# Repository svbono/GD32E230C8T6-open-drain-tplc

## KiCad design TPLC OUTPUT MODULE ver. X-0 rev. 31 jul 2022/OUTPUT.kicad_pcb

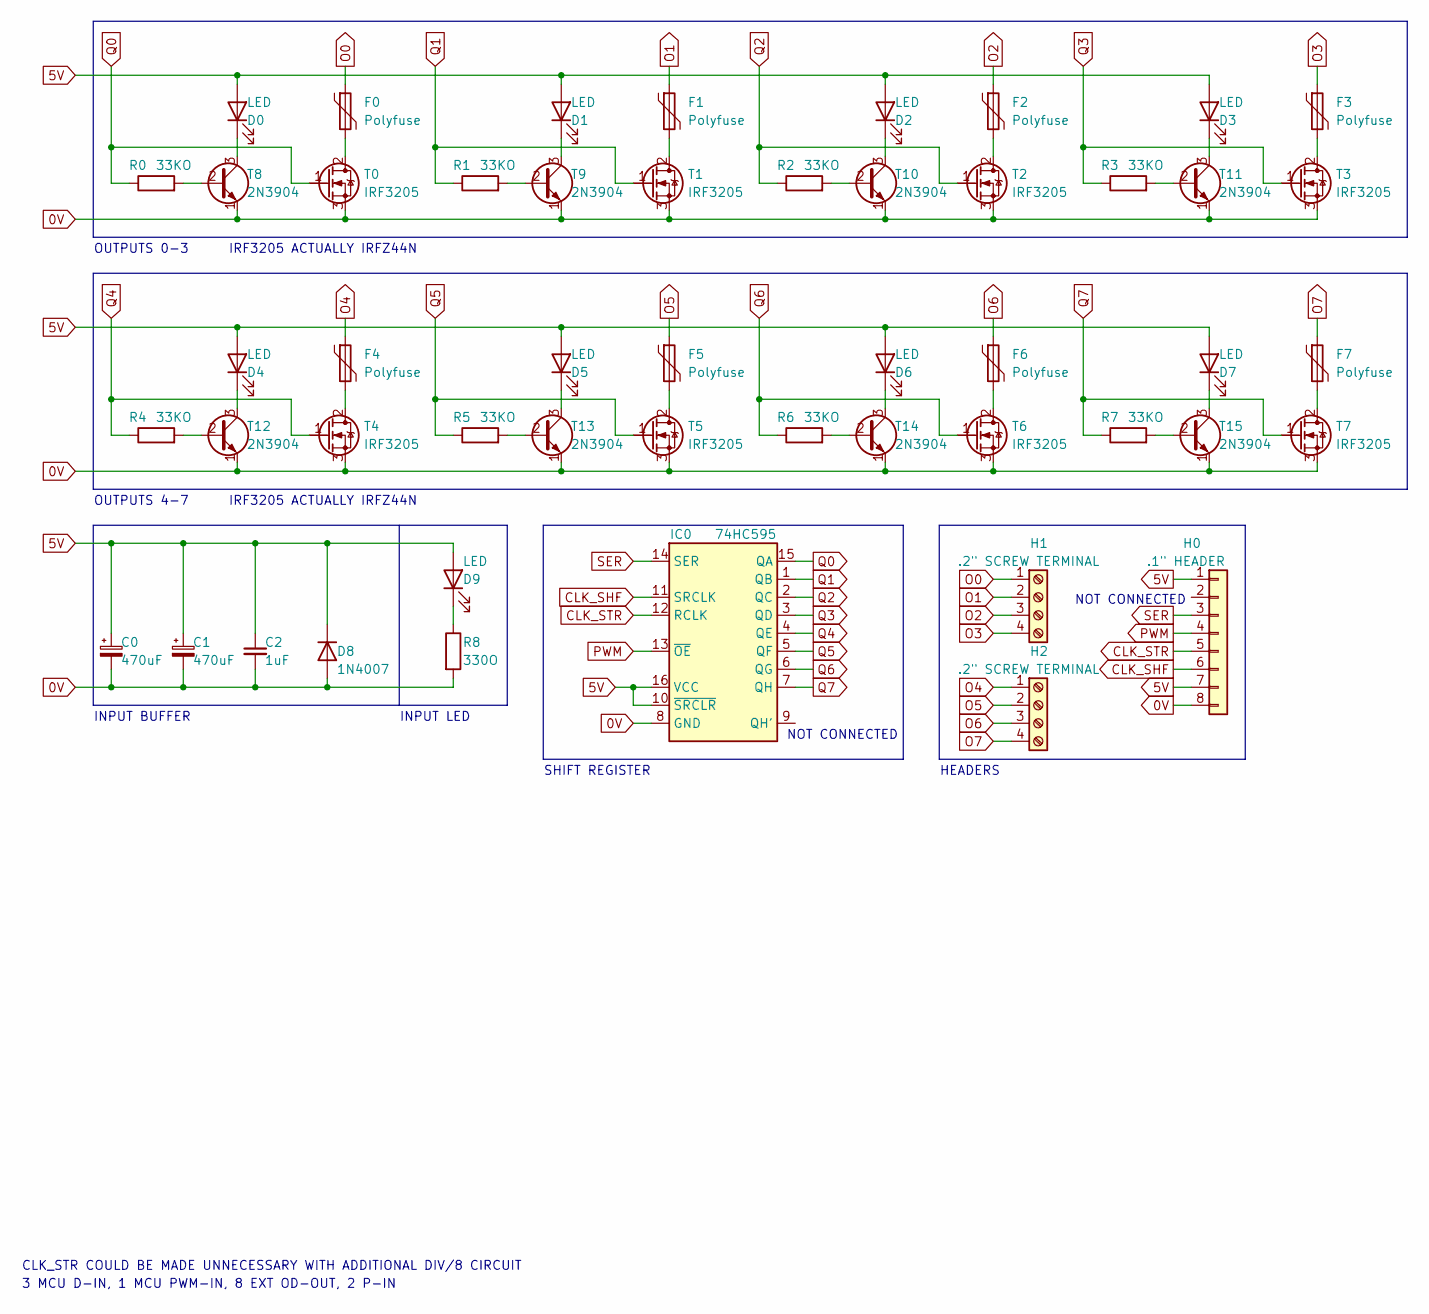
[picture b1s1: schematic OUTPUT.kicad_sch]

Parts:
C0, C1: 470uF; C_Radial_D.4in_P.1in
C2: 1uF; C_L.3in_W.1in_P.2in
D0, D1, D2, D3, D4, D5, D6, D7, D9: LED; LED_L.2in_W.1in_P.1in
D8: 1N4007; D_L.4in_W.1in_P.3in
F0, F1, F2, F3, F4, F5, F6, F7: Polyfuse; F_L1.2in_W.1in_P.4in
H0: .1" HEADER; H_1x8_P.1in
H1, H2: .2" SCREW TERMINAL; H_P.2in_4pin
IC0: 74HC595; DIP-16_W7.62mm_Short
R0, R1, R2, R3, R4, R5, R6, R7: 33KO; R_L.4in_W.1in_P.3in
R8: 330O; R_L.4in_W.1in_P.3in
T0, T1, T2, T3, T4, T5, T6, T7: IRF3205; TO-220-3_Horizontal_TabDown
T8, T9, T10, T11, T12, T13, T14, T15: 2N3904; TO-92L_Inline_Wide

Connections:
0V: C0.2, C1.2, C2.2, D8.2 (A), H0.8, IC0.8 (GND), R8.2, T0.3 (S), T1.3 (S), T2.3 (S), T3.3 (S), T4.3 (S), T5.3 (S), T6.3 (S), T7.3 (S), T8.1 (E), T9.1 (E), T10.1 (E), T11.1 (E), T12.1 (E), T13.1 (E), T14.1 (E), T15.1 (E)
3.3V: C0.1, C1.1, C2.1, D0.2 (A), D1.2 (A), D2.2 (A), D3.2 (A), D4.2 (A), D5.2 (A), D6.2 (A), D7.2 (A), D8.1 (K), D9.2 (A), H0.1, H0.7, IC0.10 (~SRCLR), IC0.16 (VCC)
CLK_SHF: H0.6, IC0.11 (SRCLK)
CLK_STR: H0.5, IC0.12 (RCLK)
unnamed: D0.1 (K), T8.3 (C)
unnamed: D1.1 (K), T9.3 (C)
unnamed: D2.1 (K), T10.3 (C)
unnamed: D3.1 (K), T11.3 (C)
unnamed: D4.1 (K), T12.3 (C)
unnamed: D5.1 (K), T13.3 (C)
unnamed: D6.1 (K), T14.3 (C)
unnamed: D7.1 (K), T15.3 (C)
unnamed: D9.1 (K), R8.1
unnamed: F0.2, T0.2 (D)
unnamed: F1.2, T1.2 (D)
unnamed: F2.2, T2.2 (D)
unnamed: F3.2, T3.2 (D)
unnamed: F4.2, T4.2 (D)
unnamed: F5.2, T5.2 (D)
unnamed: F6.2, T6.2 (D)
unnamed: F7.2, T7.2 (D)
unnamed: R0.2, T8.2 (B)
unnamed: R1.2, T9.2 (B)
unnamed: R2.2, T10.2 (B)
unnamed: R3.2, T11.2 (B)
unnamed: R4.2, T12.2 (B)
unnamed: R5.2, T13.2 (B)
unnamed: R6.2, T14.2 (B)
unnamed: R7.2, T15.2 (B)
O0: F0.1, H1.1
O1: F1.1, H1.2
O2: F2.1, H1.3
O3: F3.1, H1.4
O4: F4.1, H2.1
O5: F5.1, H2.2
O6: F6.1, H2.3
O7: F7.1, H2.4
PWM: H0.4, IC0.13 (~OE)
Q0: IC0.15 (QA), R0.1, T0.1 (G)
Q1: IC0.1 (QB), R1.1, T1.1 (G)
Q2: IC0.2 (QC), R2.1, T2.1 (G)
Q3: IC0.3 (QD), R3.1, T3.1 (G)
Q4: IC0.4 (QE), R4.1, T4.1 (G)
Q5: IC0.5 (QF), R5.1, T5.1 (G)
Q6: IC0.6 (QG), R6.1, T6.1 (G)
Q7: IC0.7 (QH), R7.1, T7.1 (G)
SER: H0.3, IC0.14 (SER)

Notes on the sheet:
IRF3205 ACTUALLY IRFZ44N
NOT CONNECTED
INPUT BUFFER
SHIFT REGISTER
INPUT LED
OUTPUTS 0-3
CLK_STR COULD BE MADE UNNECESSARY WITH ADDITIONAL DIV/8 CIRCUIT
HEADERS
OUTPUTS 4-7
3 MCU D-IN, 1 MCU PWM-IN, 8 EXT OD-OUT, 2 P-IN

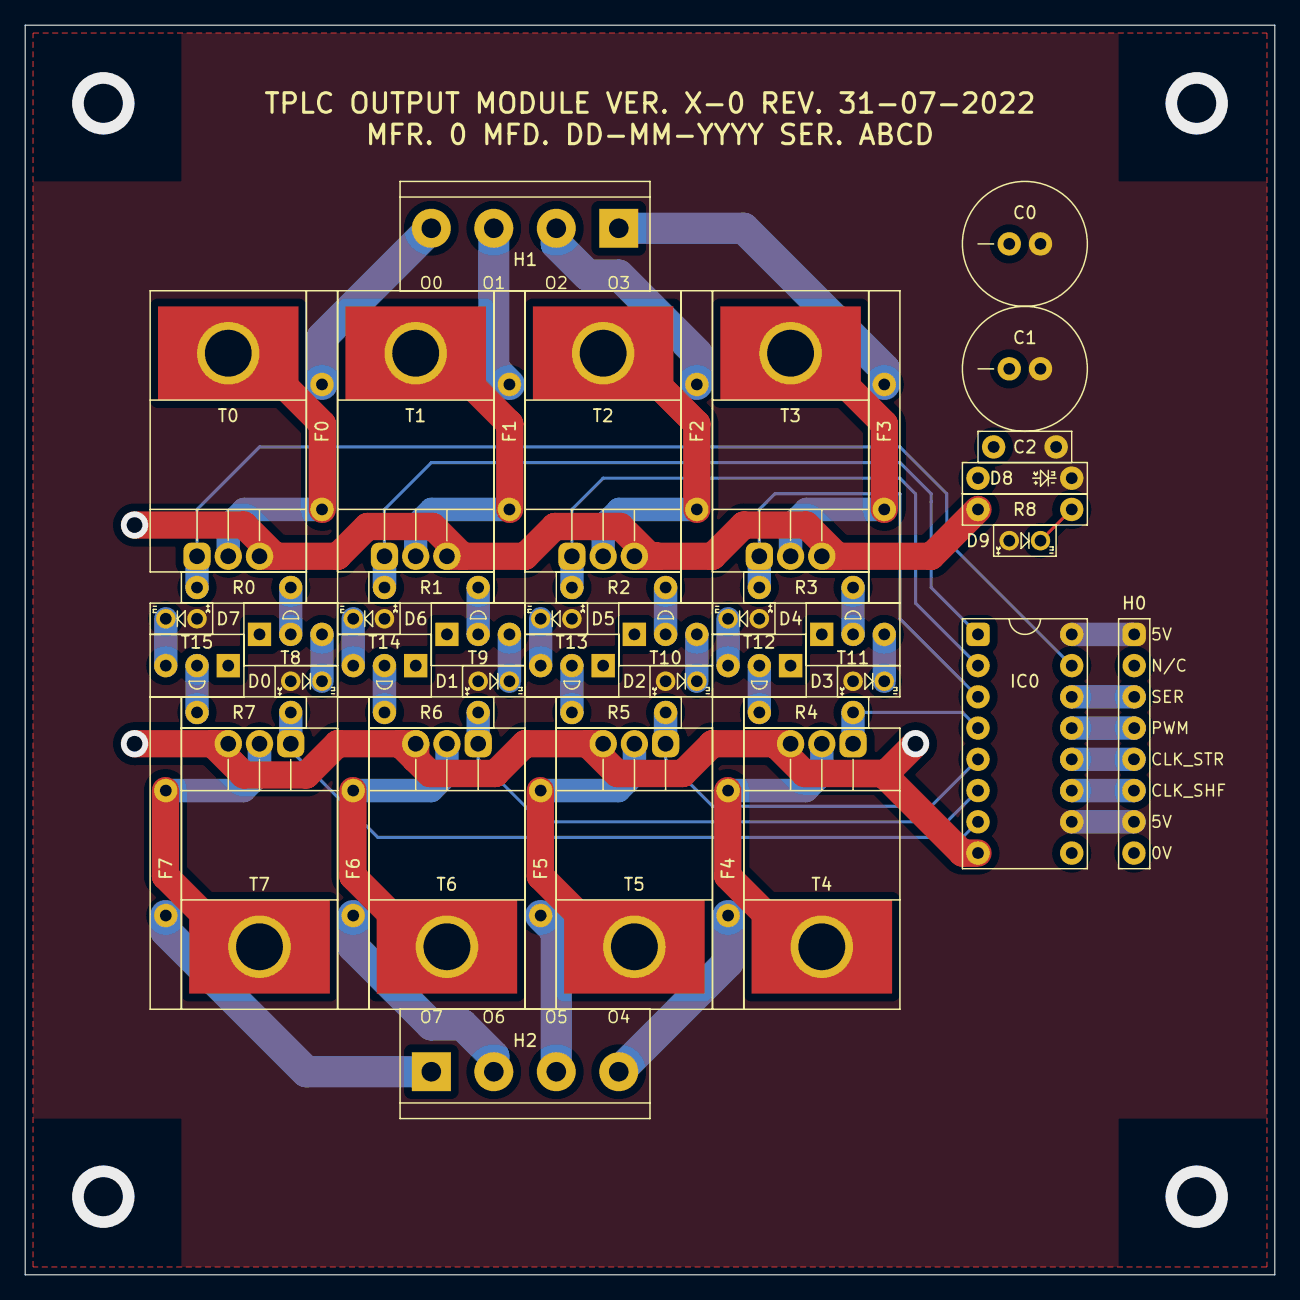
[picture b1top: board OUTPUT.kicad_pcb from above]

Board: 2 copper layers, 101.6 x 101.6 mm, 50 parts (0 on the bottom side), 47 nets.

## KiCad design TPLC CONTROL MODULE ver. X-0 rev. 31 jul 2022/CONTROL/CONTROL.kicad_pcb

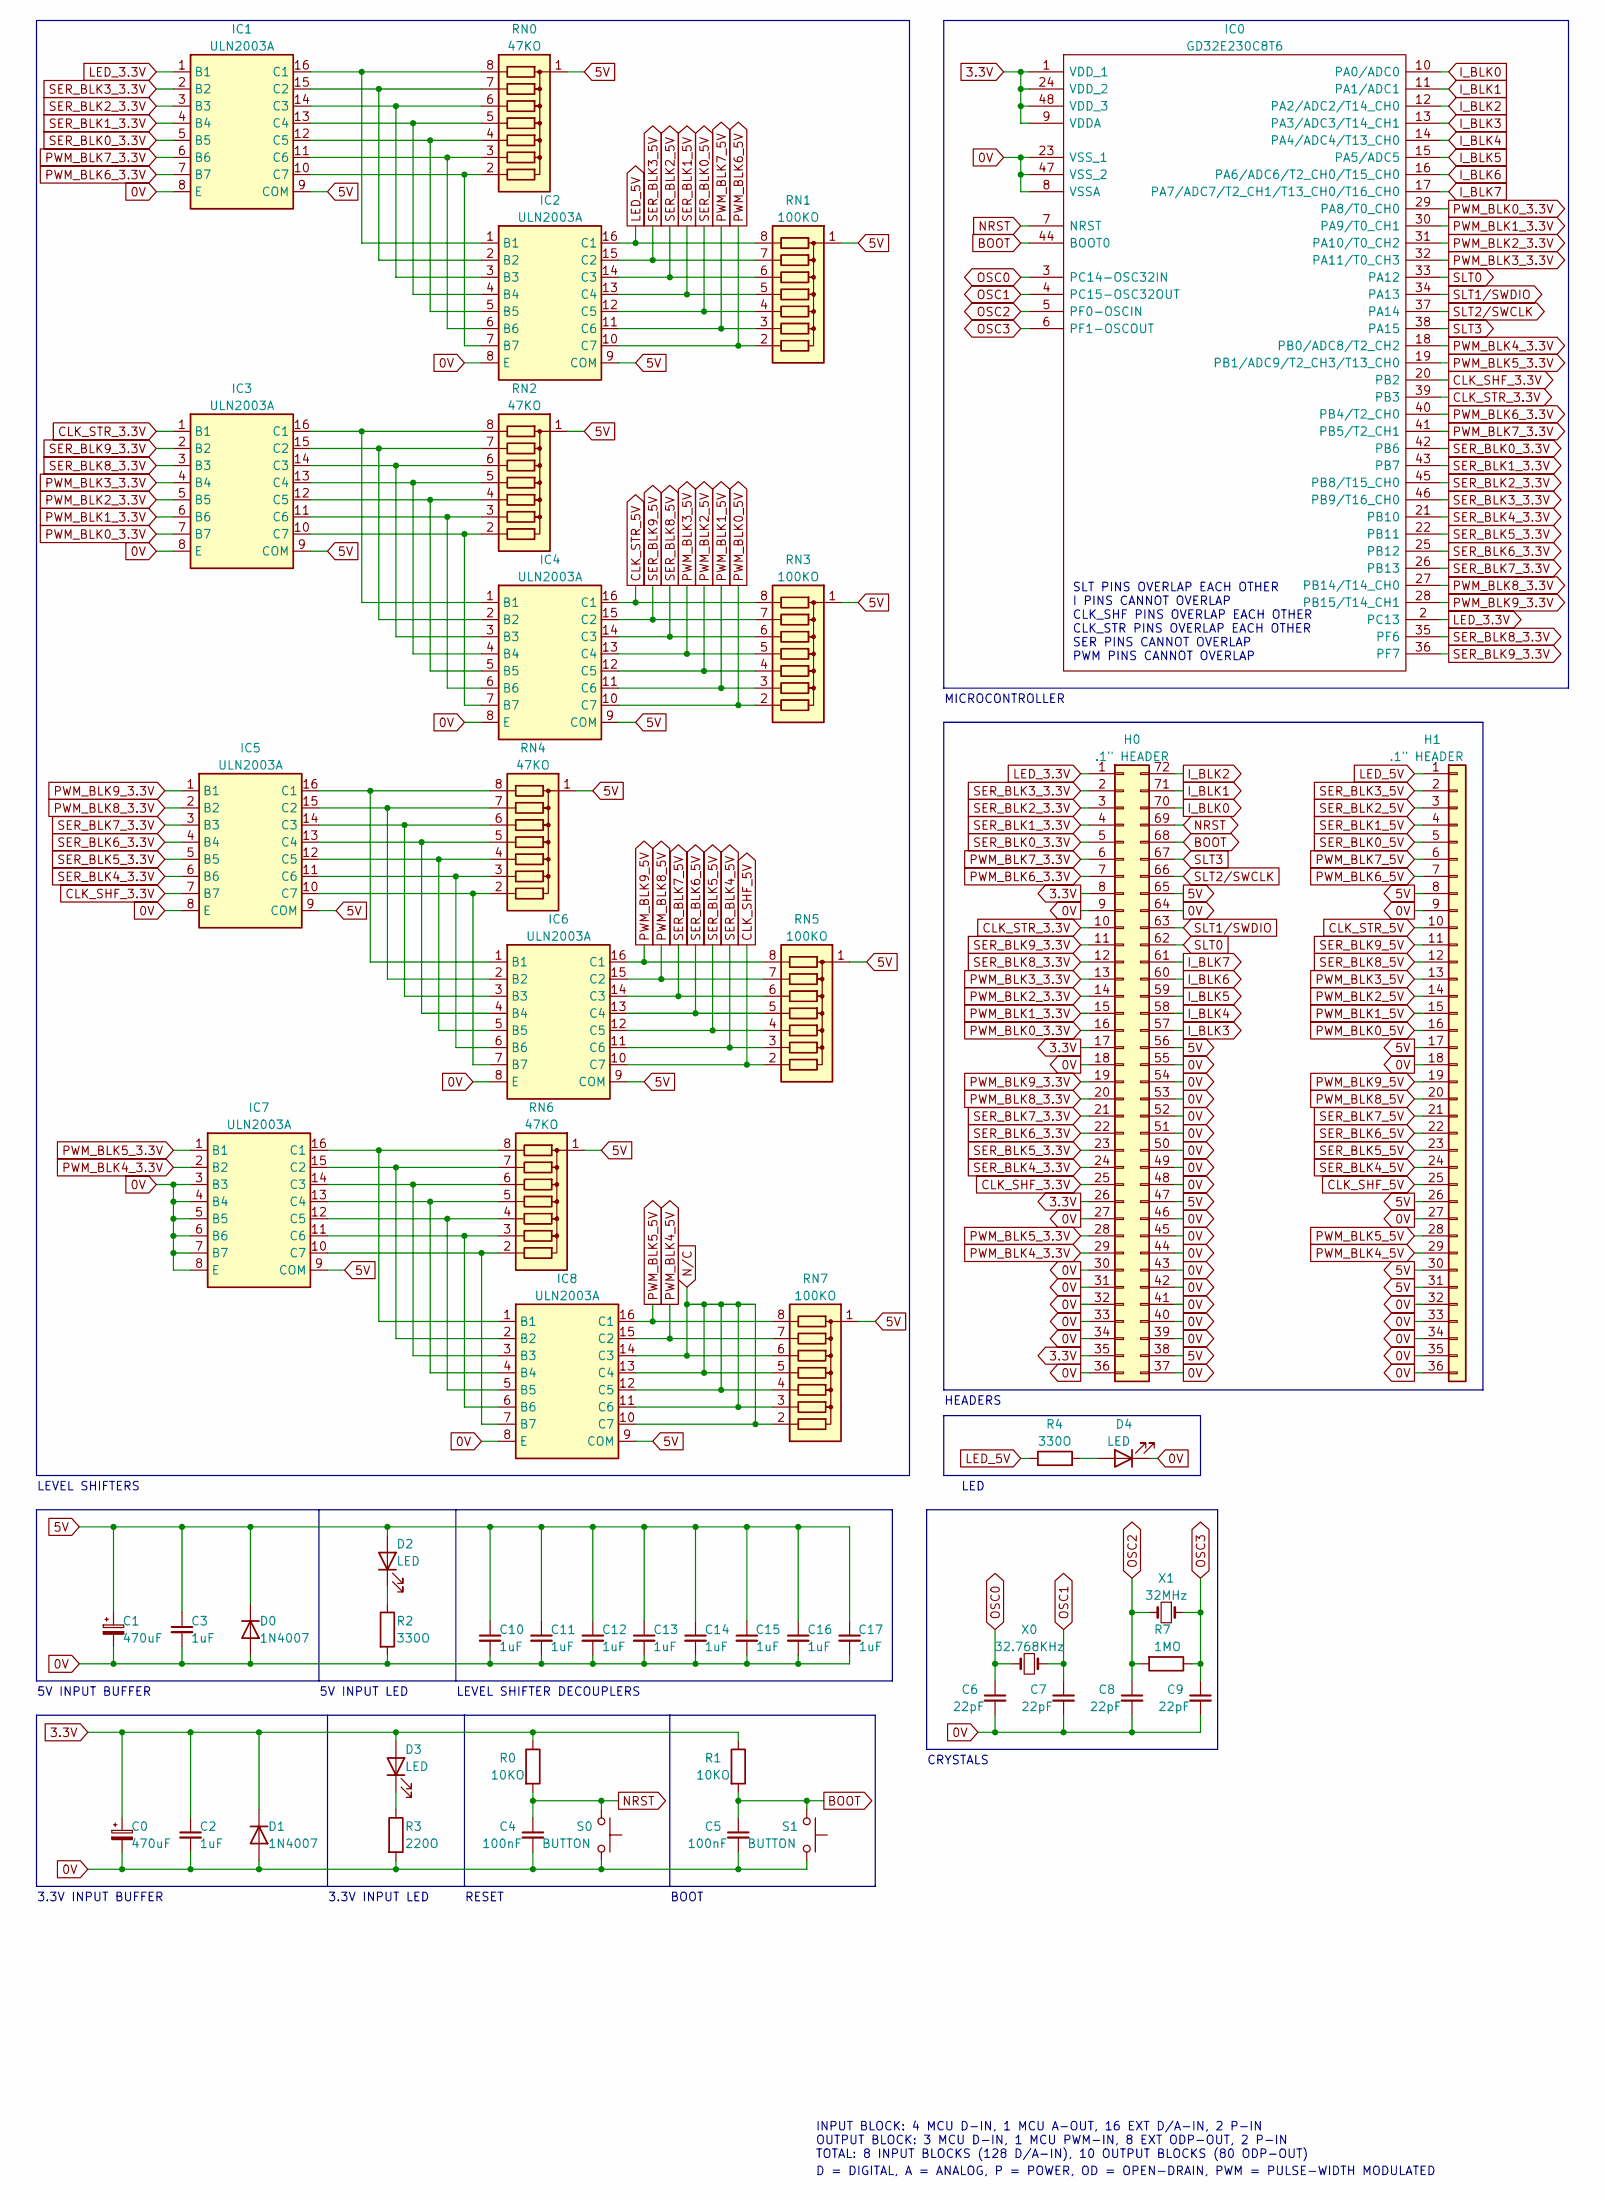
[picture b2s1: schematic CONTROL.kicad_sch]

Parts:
C0, C1: 470uF; C_Radial_D.4in_P.1in
C2, C3, C10, C11, C12, C13, C14, C15, C16, C17: 1uF; C_L.3in_W.1in_P.2in
C4, C5: 100nF; C_L.3in_W.1in_P.2in
C6, C7, C8, C9: 22pF; C_L.3in_W.1in_P.2in
D0, D1: 1N4007; D_L.4in_W.1in_P.3in
D2, D3, D4: LED; LED_L.2in_W.1in_P.1in
H0: .1" HEADER; H_2x36_P.1in
H1: .1" HEADER; H_1x36_P.1in
IC0: GD32E230C8T6; QFN-48-1EP_7x7mm_P0.5mm_EP5.15x5.15mm; Manufacturer_Part_Number GD32E230C8T6; Mouser Part Number N/A
IC1, IC2, IC3, IC4, IC5, IC6, IC7, IC8: ULN2003A; DIP-16_W7.62mm_Short
R0, R1: 10KO; R_L.4in_W.1in_P.3in
R2, R4: 330O; R_L.4in_W.1in_P.3in
R3: 220O; R_L.4in_W.1in_P.3in
R7: 1MO; R_L.4in_W.1in_P.3in
RN0, RN2, RN4, RN6: 47KO; R_SIP8
RN1, RN3, RN5, RN7: 100KO; R_SIP8
S0, S1: BUTTON; J_L.4in_W.1in_P.3in
X0: 32.768KHz; X_L.5in_W.2in_P.2in
X1: 32MHz; X_L.5in_W.2in_P.2in

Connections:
0V: C0.2, C1.2, C2.2, C3.2, C4.2, C5.2, C6.2, C7.2, C8.2, C9.2, C10.2, C11.2, C12.2, C13.2, C14.2, C15.2, C16.2, C17.2, D0.2 (A), D1.2 (A), D4.1 (K), H0.9, H0.18, H0.27, H0.30, H0.31, H0.32, H0.33, H0.34, H0.36, H0.37, H0.39, H0.40, H0.41, H0.42, H0.43, H0.44, H0.45, H0.46, H0.48, H0.49, H0.50, H0.51, H0.52, H0.53, H0.54, H0.55, H0.64, H1.9, H1.18, H1.27, H1.32, H1.33, H1.34, H1.35, H1.36, IC0.8 (VSSA), IC0.23 (VSS_1), IC0.47 (VSS_2), IC1.8 (E), IC2.8 (E), IC3.8 (E), IC4.8 (E), IC5.8 (E), IC6.8 (E), IC7.3 (B3), IC7.4 (B4), IC7.5 (B5), IC7.6 (B6), IC7.7 (B7), IC7.8 (E), IC8.8 (E), R2.2, R3.2, S0.2, S1.2
3.3V: C0.1, C2.1, D1.1 (K), D3.2 (A), H0.8, H0.17, H0.26, H0.35, IC0.1 (VDD_1), IC0.9 (VDDA), IC0.24 (VDD_2), IC0.48 (VDD_3), R0.1, R1.1
5V: C1.1, C3.1, C10.1, C11.1, C12.1, C13.1, C14.1, C15.1, C16.1, C17.1, D0.1 (K), D2.2 (A), H0.38, H0.47, H0.56, H0.65, H1.8, H1.17, H1.26, H1.30, H1.31, IC1.9 (COM), IC2.9 (COM), IC3.9 (COM), IC4.9 (COM), IC5.9 (COM), IC6.9 (COM), IC7.9 (COM), IC8.9 (COM), RN0.1 (common), RN1.1 (common), RN2.1 (common), RN3.1 (common), RN4.1 (common), RN5.1 (common), RN6.1 (common), RN7.1 (common)
BOOT: C5.1, H0.68, IC0.44 (BOOT0), R1.2, S1.1
CLK_SHF_3.3V: H0.25, IC0.20 (PB2), IC5.7 (B7)
CLK_SHF_5V: H1.25, IC6.10 (C7), RN5.2 (R7)
CLK_STR_3.3V: H0.10, IC0.39 (PB3), IC3.1 (B1)
CLK_STR_5V: H1.10, IC4.16 (C1), RN3.8 (R1)
I_BLK0: H0.70, IC0.10 (PA0/ADC0)
I_BLK1: H0.71, IC0.11 (PA1/ADC1)
I_BLK2: H0.72, IC0.12 (PA2/ADC2/T14_CH0)
I_BLK3: H0.57, IC0.13 (PA3/ADC3/T14_CH1)
I_BLK4: H0.58, IC0.14 (PA4/ADC4/T13_CH0)
I_BLK5: H0.59, IC0.15 (PA5/ADC5)
I_BLK6: H0.60, IC0.16 (PA6/ADC6/T2_CH0/T15_CH0)
I_BLK7: H0.61, IC0.17 (PA7/ADC7/T2_CH1/T13_CH0/T16_CH0)
LED_3.3V: H0.1, IC0.2 (PC13), IC1.1 (B1)
LED_5V: H1.1, IC2.16 (C1), R4.1, RN1.8 (R1)
NRST: C4.1, H0.69, IC0.7 (NRST), R0.2, S0.1
unnamed: D2.1 (K), R2.1
unnamed: D3.1 (K), R3.1
unnamed: D4.2 (A), R4.2
unnamed: IC1.10 (C7), IC2.7 (B7), RN0.2 (R7)
unnamed: IC1.11 (C6), IC2.6 (B6), RN0.3 (R6)
unnamed: IC1.12 (C5), IC2.5 (B5), RN0.4 (R5)
unnamed: IC1.13 (C4), IC2.4 (B4), RN0.5 (R4)
unnamed: IC1.14 (C3), IC2.3 (B3), RN0.6 (R3)
unnamed: IC1.15 (C2), IC2.2 (B2), RN0.7 (R2)
unnamed: IC1.16 (C1), IC2.1 (B1), RN0.8 (R1)
unnamed: IC3.10 (C7), IC4.7 (B7), RN2.2 (R7)
unnamed: IC3.11 (C6), IC4.6 (B6), RN2.3 (R6)
unnamed: IC3.12 (C5), IC4.5 (B5), RN2.4 (R5)
unnamed: IC3.13 (C4), IC4.4 (B4), RN2.5 (R4)
unnamed: IC3.14 (C3), IC4.3 (B3), RN2.6 (R3)
unnamed: IC3.15 (C2), IC4.2 (B2), RN2.7 (R2)
unnamed: IC3.16 (C1), IC4.1 (B1), RN2.8 (R1)
unnamed: IC5.10 (C7), IC6.7 (B7), RN4.2 (R7)
unnamed: IC5.11 (C6), IC6.6 (B6), RN4.3 (R6)
unnamed: IC5.12 (C5), IC6.5 (B5), RN4.4 (R5)
unnamed: IC5.13 (C4), IC6.4 (B4), RN4.5 (R4)
unnamed: IC5.14 (C3), IC6.3 (B3), RN4.6 (R3)
unnamed: IC5.15 (C2), IC6.2 (B2), RN4.7 (R2)
unnamed: IC5.16 (C1), IC6.1 (B1), RN4.8 (R1)
unnamed: IC7.10 (C7), IC8.7 (B7), RN6.2 (R7)
unnamed: IC7.11 (C6), IC8.6 (B6), RN6.3 (R6)
unnamed: IC7.12 (C5), IC8.5 (B5), RN6.4 (R5)
unnamed: IC7.13 (C4), IC8.4 (B4), RN6.5 (R4)
unnamed: IC7.14 (C3), IC8.3 (B3), RN6.6 (R3)
unnamed: IC7.15 (C2), IC8.2 (B2), RN6.7 (R2)
unnamed: IC7.16 (C1), IC8.1 (B1), RN6.8 (R1)
N/C: IC8.10 (C7), IC8.11 (C6), IC8.12 (C5), IC8.13 (C4), IC8.14 (C3), RN7.2 (R7), RN7.3 (R6), RN7.4 (R5), RN7.5 (R4), RN7.6 (R3)
OSC0: C6.1, IC0.3 (PC14-OSC32IN), X0.2
OSC1: C7.1, IC0.4 (PC15-OSC32OUT), X0.1
OSC2: C8.1, IC0.5 (PF0-OSCIN), R7.2, X1.2
OSC3: C9.1, IC0.6 (PF1-OSCOUT), R7.1, X1.1
PWM_BLK0_3.3V: H0.16, IC0.29 (PA8/T0_CH0), IC3.7 (B7)
PWM_BLK0_5V: H1.16, IC4.10 (C7), RN3.2 (R7)
PWM_BLK1_3.3V: H0.15, IC0.30 (PA9/T0_CH1), IC3.6 (B6)
PWM_BLK1_5V: H1.15, IC4.11 (C6), RN3.3 (R6)
PWM_BLK2_3.3V: H0.14, IC0.31 (PA10/T0_CH2), IC3.5 (B5)
PWM_BLK2_5V: H1.14, IC4.12 (C5), RN3.4 (R5)
PWM_BLK3_3.3V: H0.13, IC0.32 (PA11/T0_CH3), IC3.4 (B4)
PWM_BLK3_5V: H1.13, IC4.13 (C4), RN3.5 (R4)
PWM_BLK4_3.3V: H0.29, IC0.18 (PB0/ADC8/T2_CH2), IC7.2 (B2)
PWM_BLK4_5V: H1.29, IC8.15 (C2), RN7.7 (R2)
PWM_BLK5_3.3V: H0.28, IC0.19 (PB1/ADC9/T2_CH3/T13_CH0), IC7.1 (B1)
PWM_BLK5_5V: H1.28, IC8.16 (C1), RN7.8 (R1)
PWM_BLK6_3.3V: H0.7, IC0.40 (PB4/T2_CH0), IC1.7 (B7)
PWM_BLK6_5V: H1.7, IC2.10 (C7), RN1.2 (R7)
PWM_BLK7_3.3V: H0.6, IC0.41 (PB5/T2_CH1), IC1.6 (B6)
PWM_BLK7_5V: H1.6, IC2.11 (C6), RN1.3 (R6)
PWM_BLK8_3.3V: H0.20, IC0.27 (PB14/T14_CH0), IC5.2 (B2)
PWM_BLK8_5V: H1.20, IC6.15 (C2), RN5.7 (R2)
PWM_BLK9_3.3V: H0.19, IC0.28 (PB15/T14_CH1), IC5.1 (B1)
PWM_BLK9_5V: H1.19, IC6.16 (C1), RN5.8 (R1)
SER_BLK0_3.3V: H0.5, IC0.42 (PB6), IC1.5 (B5)
SER_BLK0_5V: H1.5, IC2.12 (C5), RN1.4 (R5)
SER_BLK1_3.3V: H0.4, IC0.43 (PB7), IC1.4 (B4)
SER_BLK1_5V: H1.4, IC2.13 (C4), RN1.5 (R4)
SER_BLK2_3.3V: H0.3, IC0.45 (PB8/T15_CH0), IC1.3 (B3)
SER_BLK2_5V: H1.3, IC2.14 (C3), RN1.6 (R3)
SER_BLK3_3.3V: H0.2, IC0.46 (PB9/T16_CH0), IC1.2 (B2)
SER_BLK3_5V: H1.2, IC2.15 (C2), RN1.7 (R2)
SER_BLK4_3.3V: H0.24, IC0.21 (PB10), IC5.6 (B6)
SER_BLK4_5V: H1.24, IC6.11 (C6), RN5.3 (R6)
SER_BLK5_3.3V: H0.23, IC0.22 (PB11), IC5.5 (B5)
SER_BLK5_5V: H1.23, IC6.12 (C5), RN5.4 (R5)
SER_BLK6_3.3V: H0.22, IC0.25 (PB12), IC5.4 (B4)
SER_BLK6_5V: H1.22, IC6.13 (C4), RN5.5 (R4)
SER_BLK7_3.3V: H0.21, IC0.26 (PB13), IC5.3 (B3)
SER_BLK7_5V: H1.21, IC6.14 (C3), RN5.6 (R3)
SER_BLK8_3.3V: H0.12, IC0.35 (PF6), IC3.3 (B3)
SER_BLK8_5V: H1.12, IC4.14 (C3), RN3.6 (R3)
SER_BLK9_3.3V: H0.11, IC0.36 (PF7), IC3.2 (B2)
SER_BLK9_5V: H1.11, IC4.15 (C2), RN3.7 (R2)
SLT0: H0.62, IC0.33 (PA12)
SLT1/SWDIO: H0.63, IC0.34 (PA13)
SLT2/SWCLK: H0.66, IC0.37 (PA14)
SLT3: H0.67, IC0.38 (PA15)

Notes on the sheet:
MICROCONTROLLER
LEVEL SHIFTER DECOUPLERS
SLT PINS OVERLAP EACH OTHER I PINS CANNOT OVERLAP CLK_SHF PINS OVERLAP EACH OTHER CLK_STR PINS OVERLAP EACH OTHER SER PINS CANNOT OVERLAP PWM PINS CANNOT OVERLAP
LEVEL SHIFTERS
D = DIGITAL, A = ANALOG, P = POWER, OD = OPEN-DRAIN, PWM = PULSE-WIDTH MODULATED
RESET
3.3V INPUT LED
INPUT BLOCK: 4 MCU D-IN, 1 MCU A-OUT, 16 EXT D/A-IN, 2 P-IN OUTPUT BLOCK: 3 MCU D-IN, 1 MCU PWM-IN, 8 EXT ODP-OUT, 2 P-IN TOTAL: 8 INPUT BLOCKS (128 D/A-IN), 10 OUTPUT BLOCKS (80 ODP-OUT)
5V INPUT LED
LED
5V INPUT BUFFER
CRYSTALS
BOOT
HEADERS
3.3V INPUT BUFFER

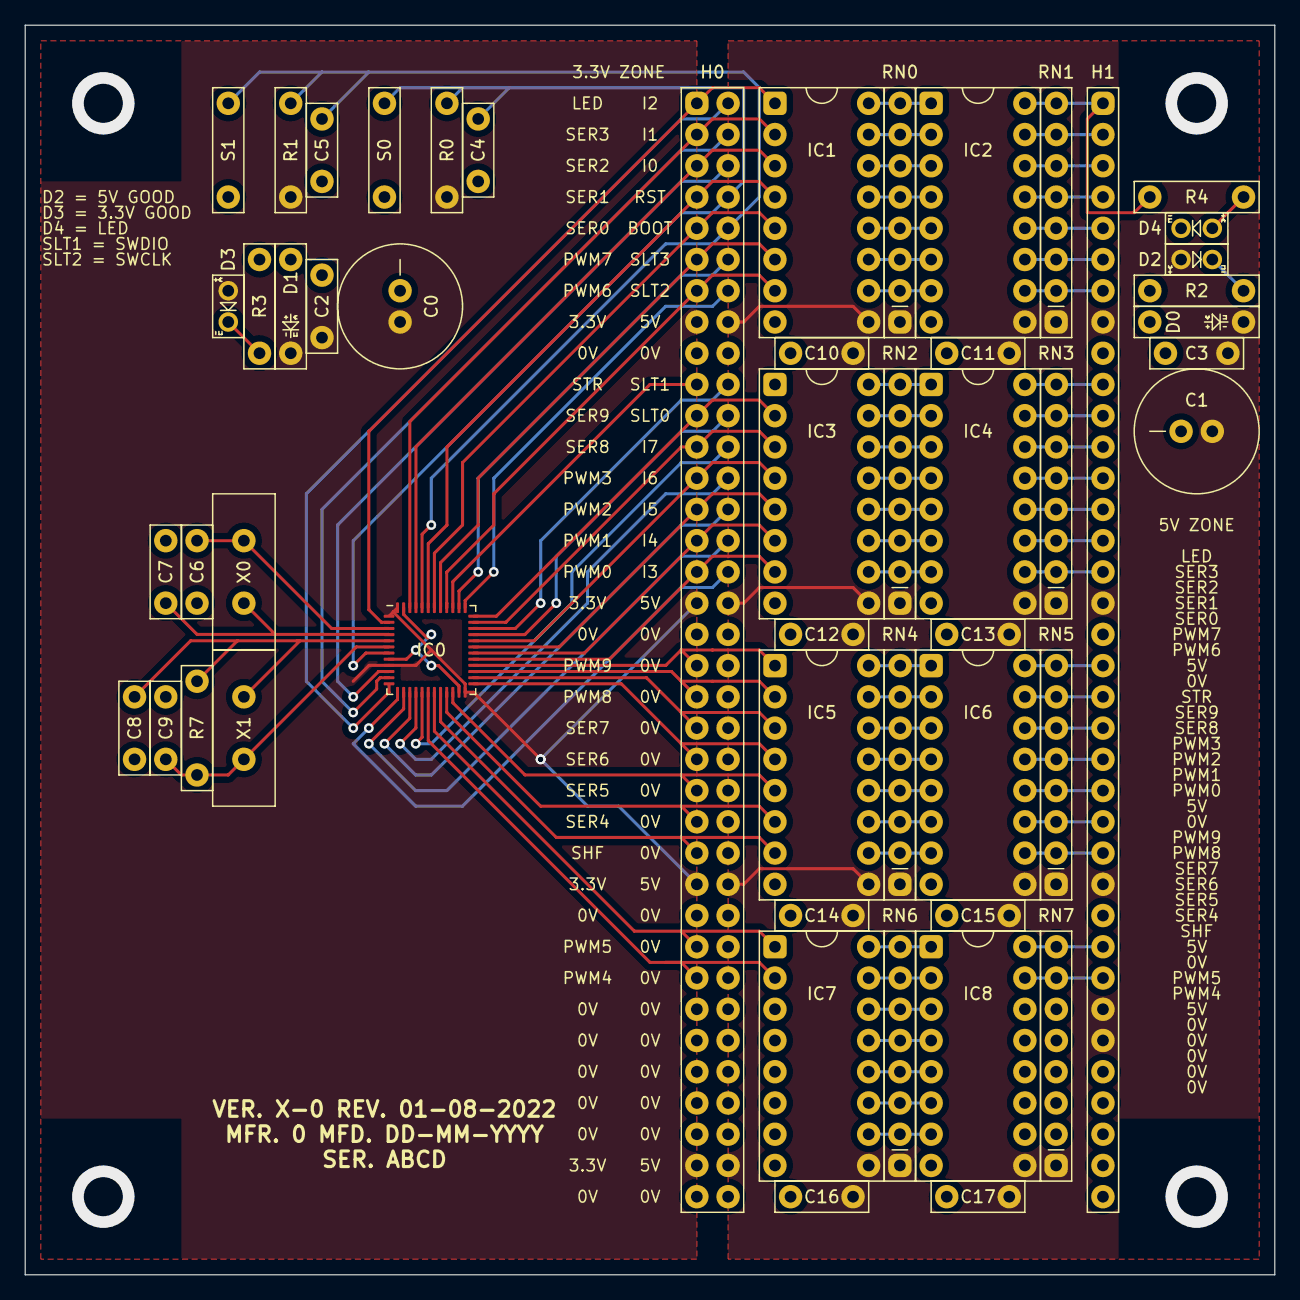
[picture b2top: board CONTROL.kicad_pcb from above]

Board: 2 copper layers, 101.6 x 101.6 mm, 52 parts (0 on the bottom side), 99 nets.

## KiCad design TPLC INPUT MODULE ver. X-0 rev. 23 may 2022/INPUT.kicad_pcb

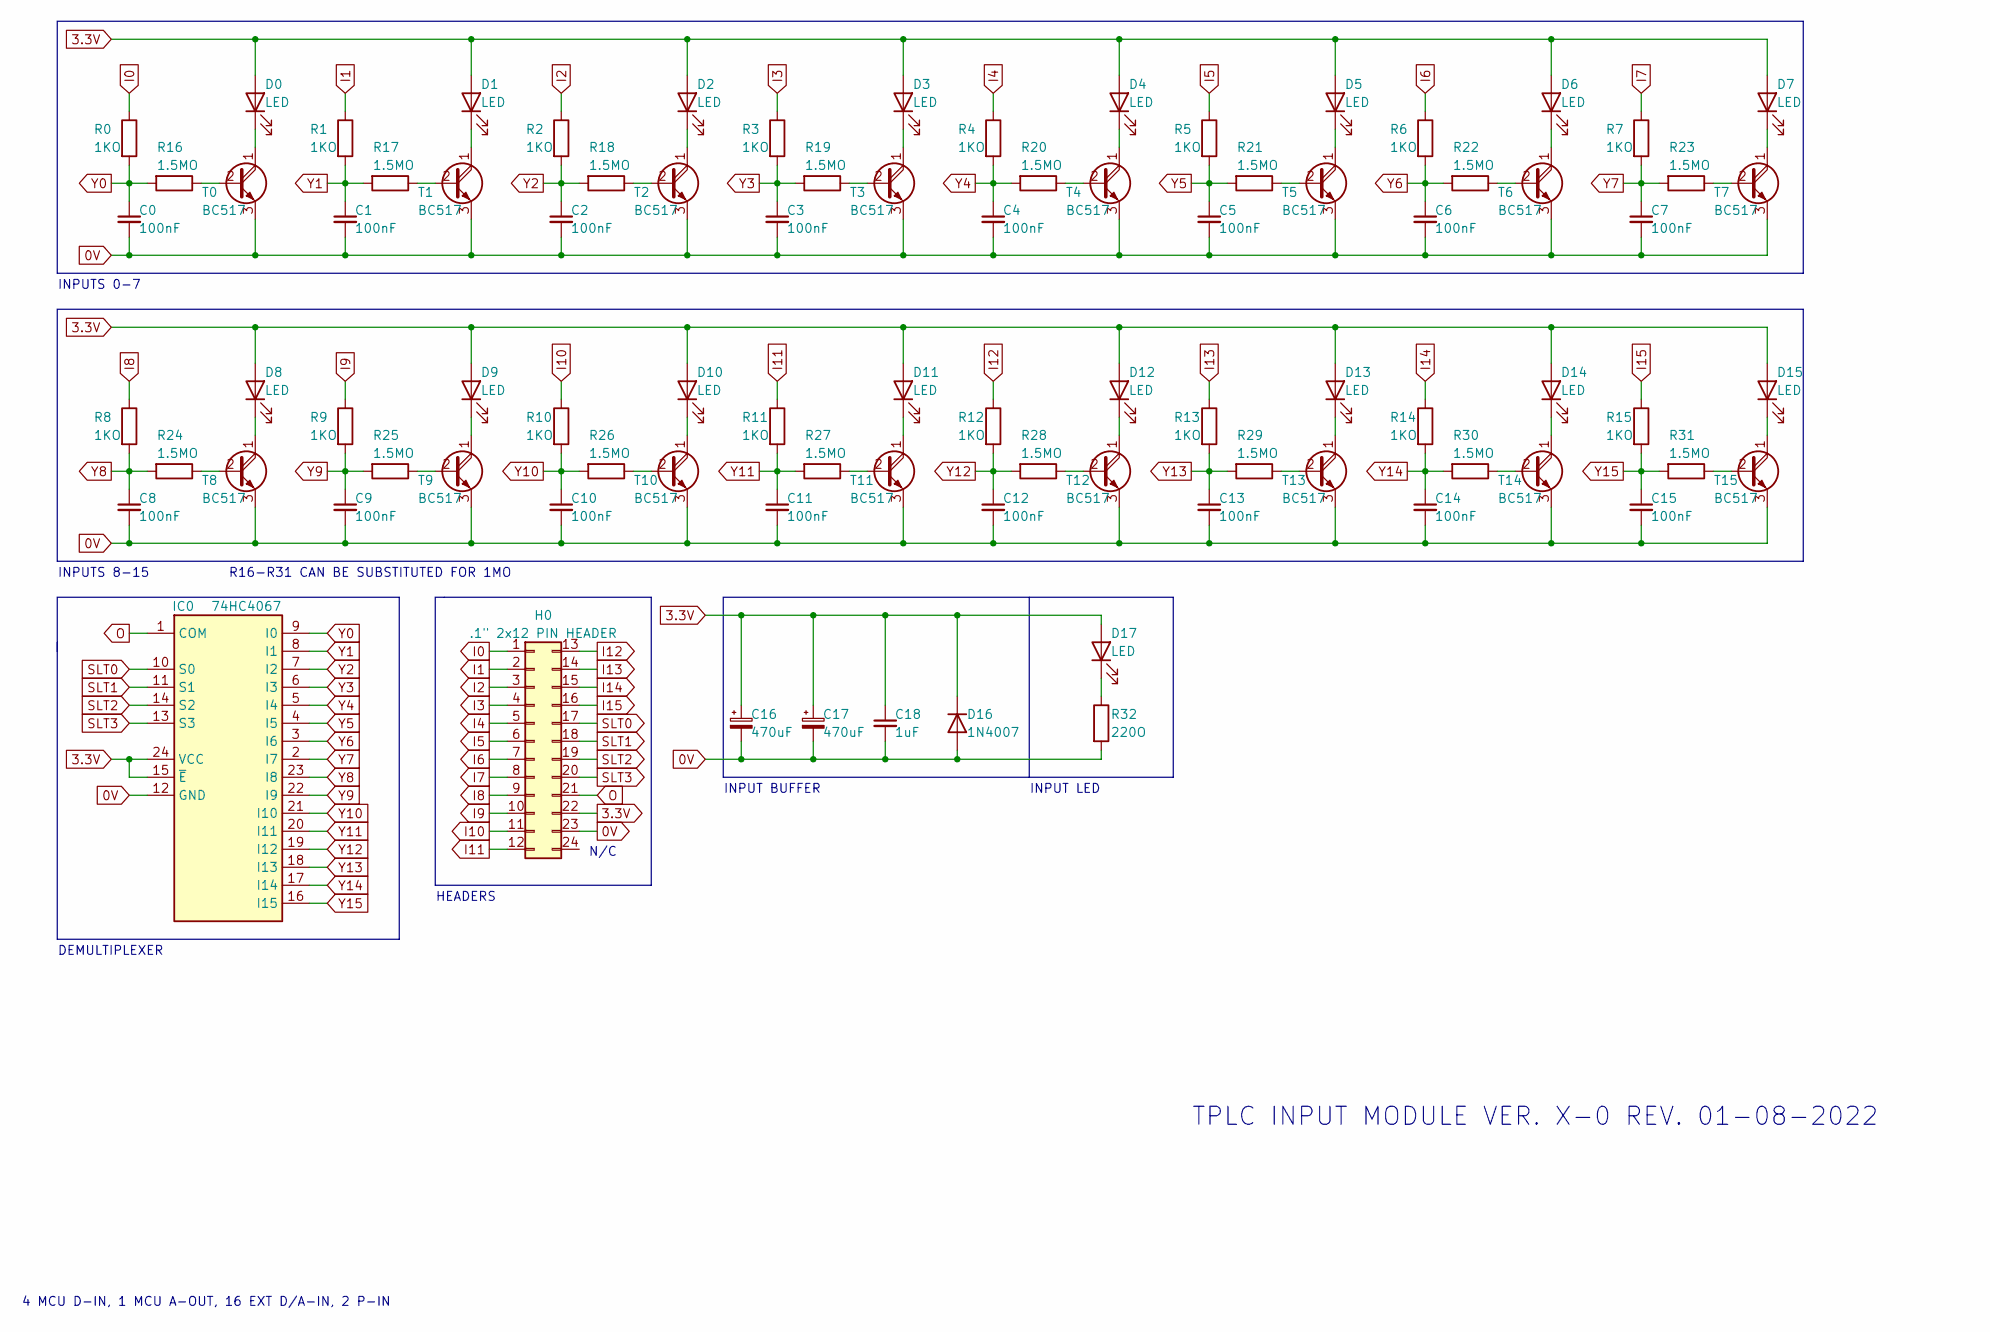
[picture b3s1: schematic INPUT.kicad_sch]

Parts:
C0, C1, C2, C3, C4, C5, C6, C7, C8, C9, C10, C11, C12, C13, C14, C15: 100nF; C_L.3in_W.1in_P.2in
C16, C17: 470uF; C_Radial_D.4in_P.1in
C18: 1uF; C_L.3in_W.1in_P.2in
D0, D1, D2, D3, D4, D5, D6, D7, D8, D9, D10, D11, D12, D13, D14, D15, D17: LED; LED_L.2in_W.1in_P.1in
D16: 1N4007; D_L.4in_W.1in_P.3in
H0: .1" 2x12 PIN HEADER; H_2x12_P.1in
IC0: 74HC4067; DIP-24_W7.62mm_Short
R0, R1, R2, R3, R4, R5, R6, R7, R8, R9, R10, R11, R12, R13, R14, R15: 1KO; R_L.4in_W.1in_P.3in
R16, R17, R18, R19, R20, R21, R22, R23, R24, R25, R26, R27, R28, R29, R30, R31: 1.5MO; R_L.4in_W.1in_P.3in
R32: 220O; R_L.4in_W.1in_P.3in
T0, T1, T2, T3, T4, T5, T6, T7, T8, T9, T10, T11, T12, T13, T14, T15: BC517; TO-92L_Inline_Wide

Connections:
0V: C0.2, C1.2, C2.2, C3.2, C4.2, C5.2, C6.2, C7.2, C8.2, C9.2, C10.2, C11.2, C12.2, C13.2, C14.2, C15.2, C16.2, C17.2, C18.2, D16.2 (A), H0.23, IC0.12 (GND), R32.2, T0.3 (E), T1.3 (E), T2.3 (E), T3.3 (E), T4.3 (E), T5.3 (E), T6.3 (E), T7.3 (E), T8.3 (E), T9.3 (E), T10.3 (E), T11.3 (E), T12.3 (E), T13.3 (E), T14.3 (E), T15.3 (E)
5V: C16.1, C17.1, C18.1, D0.2 (A), D1.2 (A), D2.2 (A), D3.2 (A), D4.2 (A), D5.2 (A), D6.2 (A), D7.2 (A), D8.2 (A), D9.2 (A), D10.2 (A), D11.2 (A), D12.2 (A), D13.2 (A), D14.2 (A), D15.2 (A), D16.1 (K), D17.2 (A), H0.22, IC0.15 (~E), IC0.24 (VCC)
I0: H0.1, R0.1
I1: H0.2, R1.1
I2: H0.3, R2.1
I3: H0.4, R3.1
I4: H0.5, R4.1
I5: H0.6, R5.1
I6: H0.7, R6.1
I7: H0.8, R7.1
I8: H0.9, R8.1
I9: H0.10, R9.1
I10: H0.11, R10.1
I11: H0.12, R11.1
I12: H0.13, R12.1
I13: H0.14, R13.1
I14: H0.15, R14.1
I15: H0.16, R15.1
unnamed: D0.1 (K), T0.1 (C)
unnamed: D1.1 (K), T1.1 (C)
unnamed: D2.1 (K), T2.1 (C)
unnamed: D3.1 (K), T3.1 (C)
unnamed: D4.1 (K), T4.1 (C)
unnamed: D5.1 (K), T5.1 (C)
unnamed: D6.1 (K), T6.1 (C)
unnamed: D7.1 (K), T7.1 (C)
unnamed: D8.1 (K), T8.1 (C)
unnamed: D9.1 (K), T9.1 (C)
unnamed: D10.1 (K), T10.1 (C)
unnamed: D11.1 (K), T11.1 (C)
unnamed: D12.1 (K), T12.1 (C)
unnamed: D13.1 (K), T13.1 (C)
unnamed: D14.1 (K), T14.1 (C)
unnamed: D15.1 (K), T15.1 (C)
unnamed: D17.1 (K), R32.1
unnamed: R16.1, T0.2 (B)
unnamed: R17.1, T1.2 (B)
unnamed: R18.1, T2.2 (B)
unnamed: R19.1, T3.2 (B)
unnamed: R20.1, T4.2 (B)
unnamed: R21.1, T5.2 (B)
unnamed: R22.1, T6.2 (B)
unnamed: R23.1, T7.2 (B)
unnamed: R24.1, T8.2 (B)
unnamed: R25.1, T9.2 (B)
unnamed: R26.1, T10.2 (B)
unnamed: R27.1, T11.2 (B)
unnamed: R28.1, T12.2 (B)
unnamed: R29.1, T13.2 (B)
unnamed: R30.1, T14.2 (B)
unnamed: R31.1, T15.2 (B)
O: H0.21, IC0.1 (COM)
SLT0: H0.17, IC0.10 (S0)
SLT1: H0.18, IC0.11 (S1)
SLT2: H0.19, IC0.14 (S2)
SLT3: H0.20, IC0.13 (S3)
Y0: C0.1, IC0.9 (I0), R0.2, R16.2
Y1: C1.1, IC0.8 (I1), R1.2, R17.2
Y2: C2.1, IC0.7 (I2), R2.2, R18.2
Y3: C3.1, IC0.6 (I3), R3.2, R19.2
Y4: C4.1, IC0.5 (I4), R4.2, R20.2
Y5: C5.1, IC0.4 (I5), R5.2, R21.2
Y6: C6.1, IC0.3 (I6), R6.2, R22.2
Y7: C7.1, IC0.2 (I7), R7.2, R23.2
Y8: C8.1, IC0.23 (I8), R8.2, R24.2
Y9: C9.1, IC0.22 (I9), R9.2, R25.2
Y10: C10.1, IC0.21 (I10), R10.2, R26.2
Y11: C11.1, IC0.20 (I11), R11.2, R27.2
Y12: C12.1, IC0.19 (I12), R12.2, R28.2
Y13: C13.1, IC0.18 (I13), R13.2, R29.2
Y14: C14.1, IC0.17 (I14), R14.2, R30.2
Y15: C15.1, IC0.16 (I15), R15.2, R31.2

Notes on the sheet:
INPUT BUFFER
HEADERS
INPUTS 0-7
R16-R31 CAN BE SUBSTITUTED FOR 1MO
4 MCU D-IN, 1 MCU A-OUT, 16 EXT D/A-IN, 2 P-IN
INPUT LED
DEMULTIPLEXER
INPUTS 8-15
N/C
TPLC INPUT MODULE VER. X-0 REV. 01-08-2022

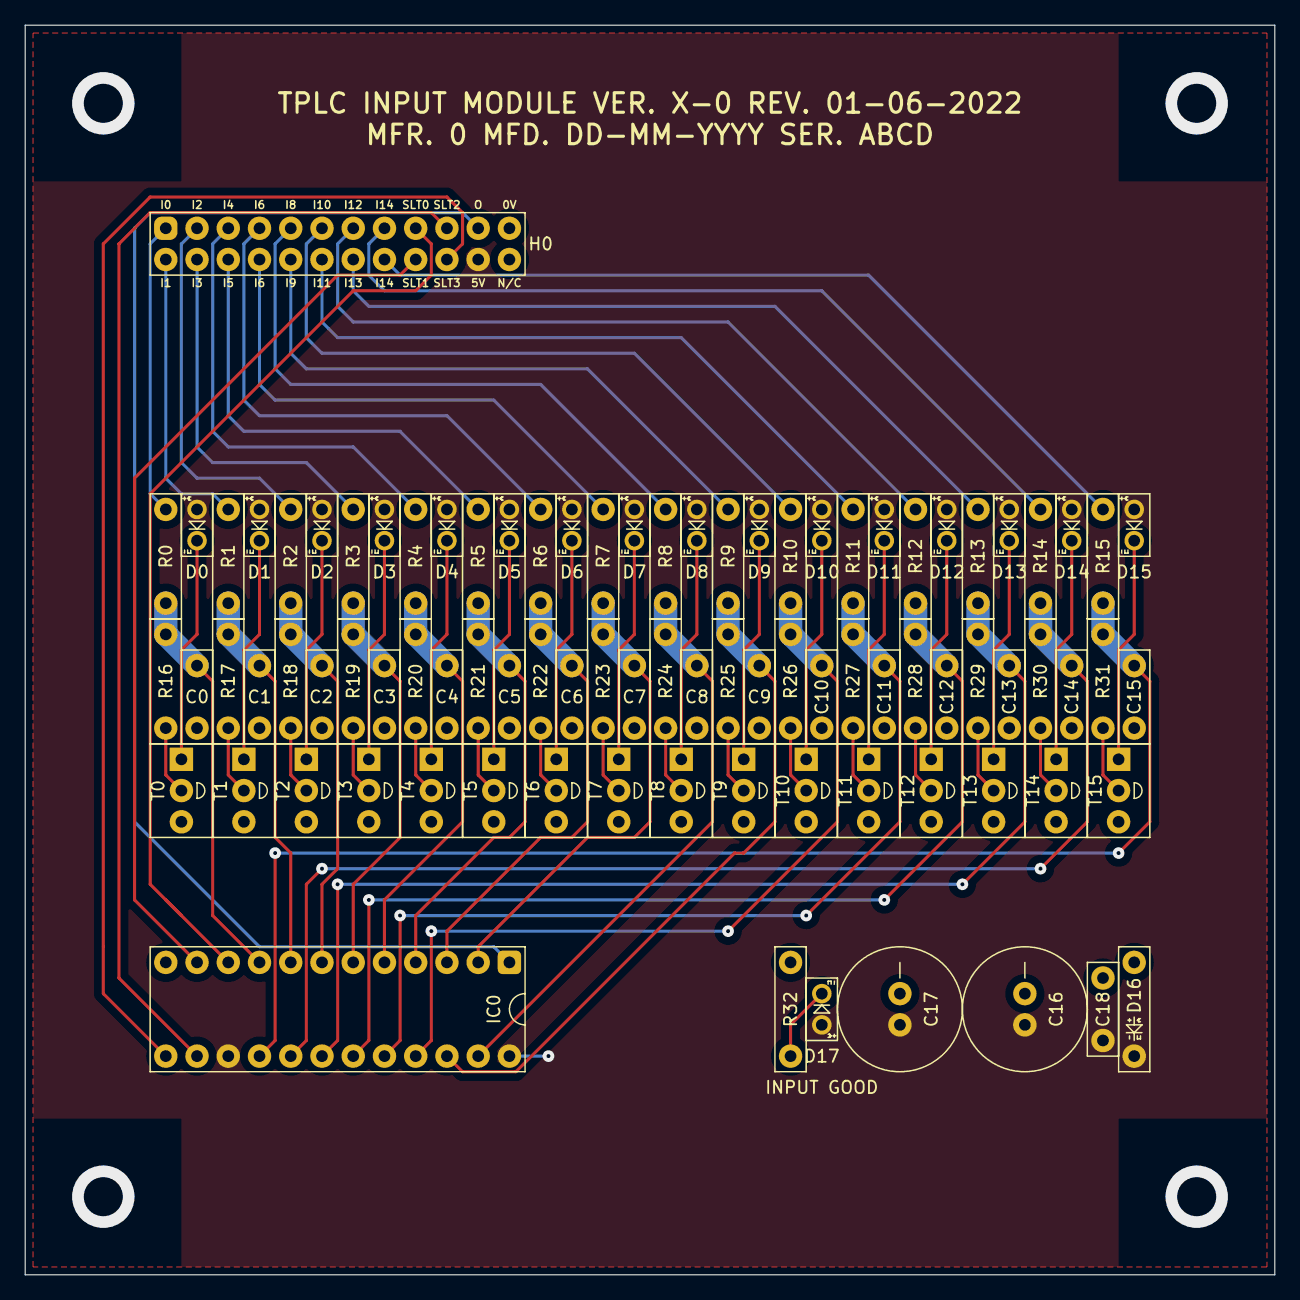
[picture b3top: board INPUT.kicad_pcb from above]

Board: 2 copper layers, 101.6 x 101.6 mm, 88 parts (0 on the bottom side), 72 nets.

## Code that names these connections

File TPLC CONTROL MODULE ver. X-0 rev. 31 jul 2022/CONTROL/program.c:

//this program is nowhere near done, consult paper notes for details

//analog inputs
//x = block (8 blocks)
//y = block sub-pin (16 per block)
int in[][] =
{
	{0, 0, 0, 0, 0, 0, 0, 0, 0, 0, 0, 0, 0, 0, 0, 0},
	{0, 0, 0, 0, 0, 0, 0, 0, 0, 0, 0, 0, 0, 0, 0, 0},
	{0, 0, 0, 0, 0, 0, 0, 0, 0, 0, 0, 0, 0, 0, 0, 0},
	{0, 0, 0, 0, 0, 0, 0, 0, 0, 0, 0, 0, 0, 0, 0, 0},
	{0, 0, 0, 0, 0, 0, 0, 0, 0, 0, 0, 0, 0, 0, 0, 0},
	{0, 0, 0, 0, 0, 0, 0, 0, 0, 0, 0, 0, 0, 0, 0, 0},
	{0, 0, 0, 0, 0, 0, 0, 0, 0, 0, 0, 0, 0, 0, 0, 0},
	{0, 0, 0, 0, 0, 0, 0, 0, 0, 0, 0, 0, 0, 0, 0, 0}
};

//digital outputs
//x = block (10 blocks)
//y = block sub-pin (8 per block)
bool out[][] =
{
	{0, 0, 0, 0, 0, 0, 0, 0},
	{0, 0, 0, 0, 0, 0, 0, 0},
	{0, 0, 0, 0, 0, 0, 0, 0},
	{0, 0, 0, 0, 0, 0, 0, 0},
	{0, 0, 0, 0, 0, 0, 0, 0},
	{0, 0, 0, 0, 0, 0, 0, 0},
	{0, 0, 0, 0, 0, 0, 0, 0},
	{0, 0, 0, 0, 0, 0, 0, 0},
	{0, 0, 0, 0, 0, 0, 0, 0},
	{0, 0, 0, 0, 0, 0, 0, 0}
};

//pwm outputs
//x = block (10 blocks)
int pwm[] = {0, 0, 0, 0, 0, 0, 0, 0, 0, 0};

//slt states
//x = pin
//y = pin (4 pins)
bool slt[][] =
{
	{0, 0, 0, 0},
	{0, 0, 0, 1},
	{0, 0, 1, 0},
	{0, 0, 1, 1},
	{0, 1, 0, 0},
	{0, 1, 0, 1},
	{0, 1, 1, 0},
	{0, 1, 1, 1},
	{1, 0, 0, 0},
	{1, 0, 0, 1},
	{1, 0, 1, 0},
	{1, 0, 1, 1},
	{1, 1, 0, 0},
	{1, 1, 0, 1},
	{1, 1, 1, 0},
	{1, 1, 1, 1}
};




//read function (16 timepulses)
void read()
{
	//write to "in" matrix from demux
	for(y = 0; y <= 15; y++)	//advance to next sub-pin
	{
		//read inputs from the given sub-pins of each block and write it to "in" matrix 
		analogRead(pin_i_blk0, in[0][y]);
		analogRead(pin_i_blk1, in[1][y]);
		analogRead(pin_i_blk2, in[2][y]);
		analogRead(pin_i_blk3, in[3][y]);
		analogRead(pin_i_blk4, in[4][y]);
		analogRead(pin_i_blk5, in[5][y]);
		analogRead(pin_i_blk6, in[6][y]);
		analogRead(pin_i_blk7, in[7][y]);
		delay(timepulse);
	}
}

//write function (17 timepulses)
void write()
{
	//write to shift register from out[][] (16 timepulses)
	for(y = 0; y <= 7; y++)	//advance to next sub-pin
	{
		//read out[][] for the given sub-pins of each block and write it to shift register
		digitalWrite(pin_ser_blk0, out[0][y]);
		digitalWrite(pin_ser_blk1, out[1][y]);
		digitalWrite(pin_ser_blk2, out[2][y]);
		digitalWrite(pin_ser_blk3, out[3][y]);
		digitalWrite(pin_ser_blk4, out[4][y]);
		digitalWrite(pin_ser_blk5, out[5][y]);
		digitalWrite(pin_ser_blk6, out[6][y]);
		digitalWrite(pin_ser_blk7, out[7][y]);
		digitalWrite(pin_ser_blk8, out[8][y]);
		digitalWrite(pin_ser_blk9, out[9][y]);
		//pulse clk_shf to write serial inputs to shift register
		digitalWrite(pin_clk_shf, 0);
		delay(timepulse);
		digitalWrite(pin_clk_shf, 1);
		delay(timepulse);
	}
	//pulse clk_str to write shift register outputs to register (1 timepulse)
	//pin_clk_str is inverted because it's driving a ~clk_str pin on the 74HC595
	digitalWrite(pin_clk_str, 1);
	delay(timepulse);
	digitalWrite(pin_clk_str, 0);
	//read pwm[] for the given block and write to respective pwm pins
	//pwm is inverted because it's driving an O/D pin on the 74HC595
	//255 was used for atmega328p, new number needed for new MCU
	analogWrite(pin_pwm_blk0, 255 - pwm[0]);
	analogWrite(pin_pwm_blk1, 255 - pwm[1]);
	analogWrite(pin_pwm_blk2, 255 - pwm[2]);
	analogWrite(pin_pwm_blk3, 255 - pwm[3]);
	analogWrite(pin_pwm_blk4, 255 - pwm[4]);
	analogWrite(pin_pwm_blk5, 255 - pwm[5]);
	analogWrite(pin_pwm_blk6, 255 - pwm[6]);
	analogWrite(pin_pwm_blk7, 255 - pwm[7]);
	analogWrite(pin_pwm_blk8, 255 - pwm[8]);
	analogWrite(pin_pwm_blk9, 255 - pwm[9]);
}

//orders (calculates out[][] and pwm[] as a function of in[][])
//if input voltage is above ~2.5 V at an input pin, set corresponding output pin high
//pwm for each output block is determined by the voltage of the first pin of it's block
//needs to be reworked for new MCU
void orders()
{
	//calculate pwm
	pwm[0] = in[0][0] / 4;
	pwm[1] = in[0][7] / 4;
	pwm[2] = in[1][0] / 4;
	pwm[3] = in[1][7] / 4;
	

	//calculate out
	for(y = 0; y <= 7; y++)
	{
		if(in[0][y] < 127)
		{
			out[0][y];
		}
		if(in[0][y + 8] < 127)
		{
			out[1][y];
		}
		if(in[1][y] < 127)
		{
			out[2][y];
		}
		if(in[1][y + 8] < 127)
		{
			out[3][y];
		}
	}
}

//program
void loop()
{
	//wait time
	delay(950);

	//read inputs
	read();

	//execute orders
	orders();

	//write outputs
	write();
}

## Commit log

2023-06-08 Add files via upload
    Added all files which exist to date.
2023-06-08 Delete TPLC CONTROL MODULE ver. X-0 rev. 31 jul 2022/CONTROL/CONTROL-backups directory
    Deleted unnecessary backups.
2023-06-08 Delete TPLC OUTPUT MODULE ver. X-0 rev. 31 jul 2022/OUTPUT-backups directory
    Deleted unnecessary backups.
